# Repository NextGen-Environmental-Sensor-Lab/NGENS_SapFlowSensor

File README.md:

# NGENS_SapFlowSensor

Kicad files for NEXTGEN SENSOR LAB version of Justin Beslity's Sap Flow Sensor. 

Kicad download https://www.kicad.org/download/
Start with file SFS_NGENS_V1.1.kicad_pro

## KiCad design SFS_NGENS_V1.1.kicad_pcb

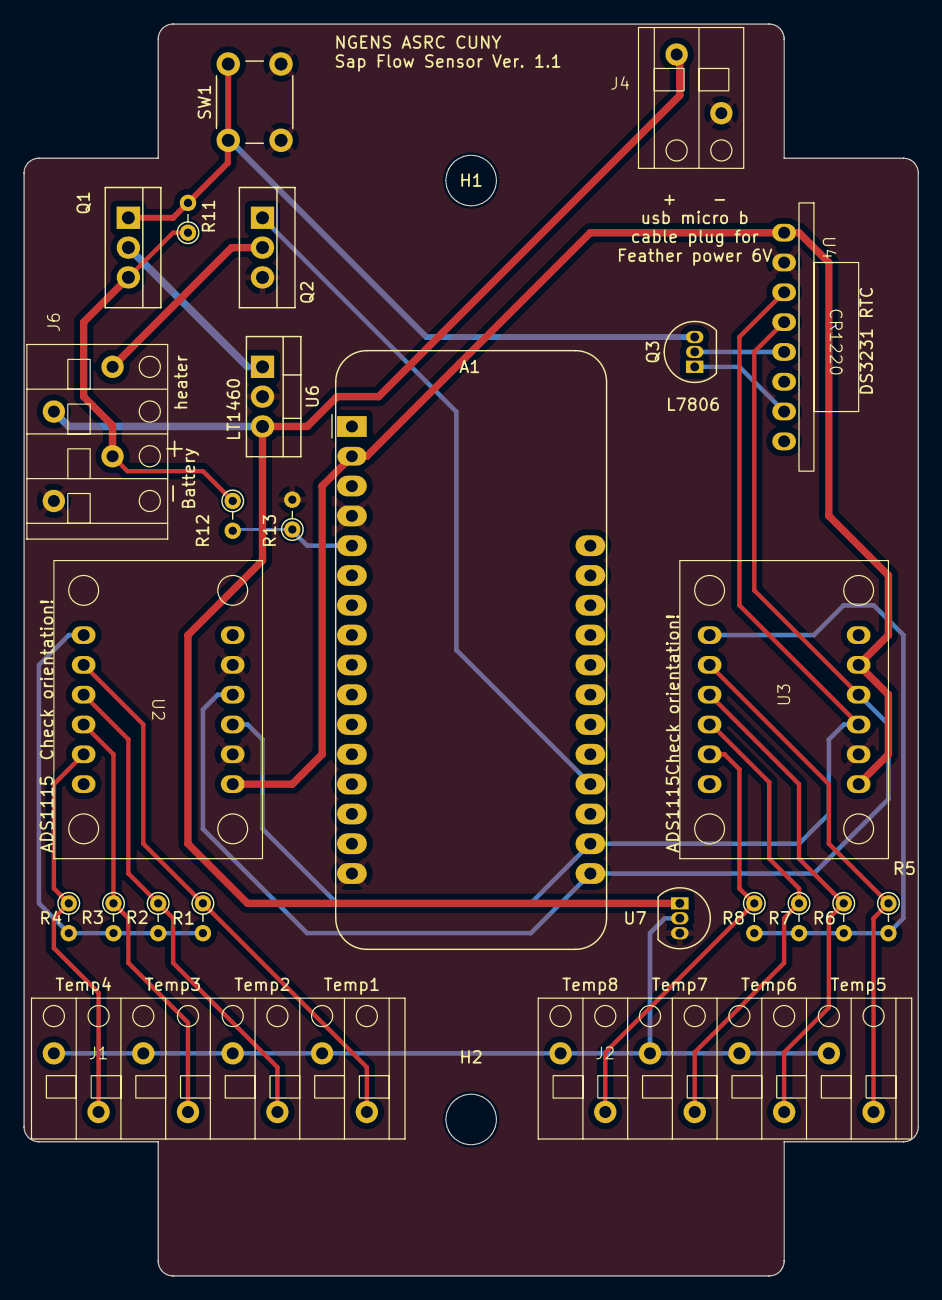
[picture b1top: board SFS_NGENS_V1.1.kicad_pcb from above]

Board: 2 copper layers, 76.2 x 106.7 mm, 27 parts (0 on the bottom side), 24 nets.

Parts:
A1: Adafruit_Feather_M0_Adalogger; Adafruit_Feather
H1, H2: MountingHole; MountingHole_4.3mm_M4
J1, J2: Screw_Terminal_01x08; Wurth_Screwless45_3.81mm_8
J4: Screw_Terminal_01x02; Wurth_Screwless45_3.81mm_2
J6: Screw_Terminal_01x04; Wurth_Screwless45_3.81mm_4
Q1: IRF9540N; TO-262-3_Vertical
Q2: RFP30N06LE; TO-262-3_Vertical
Q3: 2N7000; TO-92_Inline
R1, R2, R3, R4, R5, R6, R7, R8, R13: 10k; R_Axial_DIN0204_L3.6mm_D1.6mm_P2.54mm_Vertical
R11: 100K; R_Axial_DIN0204_L3.6mm_D1.6mm_P2.54mm_Vertical
R12: 100k; R_Axial_DIN0204_L3.6mm_D1.6mm_P2.54mm_Vertical
SW1: SW_Push; SW_PUSH_6mm_H4.3mm
U2, U3: ADS1115_Breakout
U4: DS3231_Breakout_RightAngle
U6: L7806; TO-220-3_Vertical
U7: TO-92_Inline

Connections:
+3V3: A1.2 (3V3), U2.1 (VIN), U3.1 (VIN), U3.5 (ADDR), U4.1 (Vin)
+6V: J4.2, J6.2, U6.3 (OUT), U7.1 (Vin)
GND: A1.4 (GND), A1.16 (GND), J4.1, J6.4, Q2.3 (S), R13.2, SW1.2, U2.2 (GND), U2.5 (ADDR), U3.2 (GND), U4.2 (GND), U6.2 (GND), U7.3 (GND)
HEAT: A1.20 (D6), Q2.1 (G)
unnamed: A1.5 (DAC0/A0), R12.2, R13.1
unnamed: J1.1, J1.3, J1.5, J1.7, J2.1, J2.3, J2.5, J2.7, U7.2 (Vout)
unnamed: J1.2, R4.1, U2.11 (A3)
unnamed: J1.4, R3.1, U2.10 (A2)
unnamed: J1.6, R2.1, U2.9 (A1)
unnamed: J1.8, R1.1, U2.8 (A0)
unnamed: J2.2, R8.1, U3.11 (A3)
unnamed: J2.4, R7.1, U3.10 (A2)
unnamed: J2.6, R6.1, U3.9 (A1)
unnamed: J2.8, R5.1, U3.8 (A0)
unnamed: J6.1, Q2.2 (D)
unnamed: J6.3, Q1.3 (S), R11.1, R12.1
unnamed: Q1.2 (D), U6.1 (IN)
unnamed: Q1.1 (G), Q3.3 (D), R11.2, SW1.1
unnamed: Q3.2 (G), U4.5 (BAT)
unnamed: Q3.1 (S), U4.7 (SQW)
unnamed: R1.2, R2.2, R3.2, R4.2, U2.7 (A-)
unnamed: R5.2, R6.2, R7.2, R8.2, U3.7 (A-)
SCL: A1.18 (SCL/D21), U2.3 (SCL), U3.3 (SCL), U4.3 (SCL)
SDA: A1.17 (SDA/D20), U2.4 (SDA), U3.4 (SDA), U4.4 (SDA)

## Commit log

2024-03-01 images commit
